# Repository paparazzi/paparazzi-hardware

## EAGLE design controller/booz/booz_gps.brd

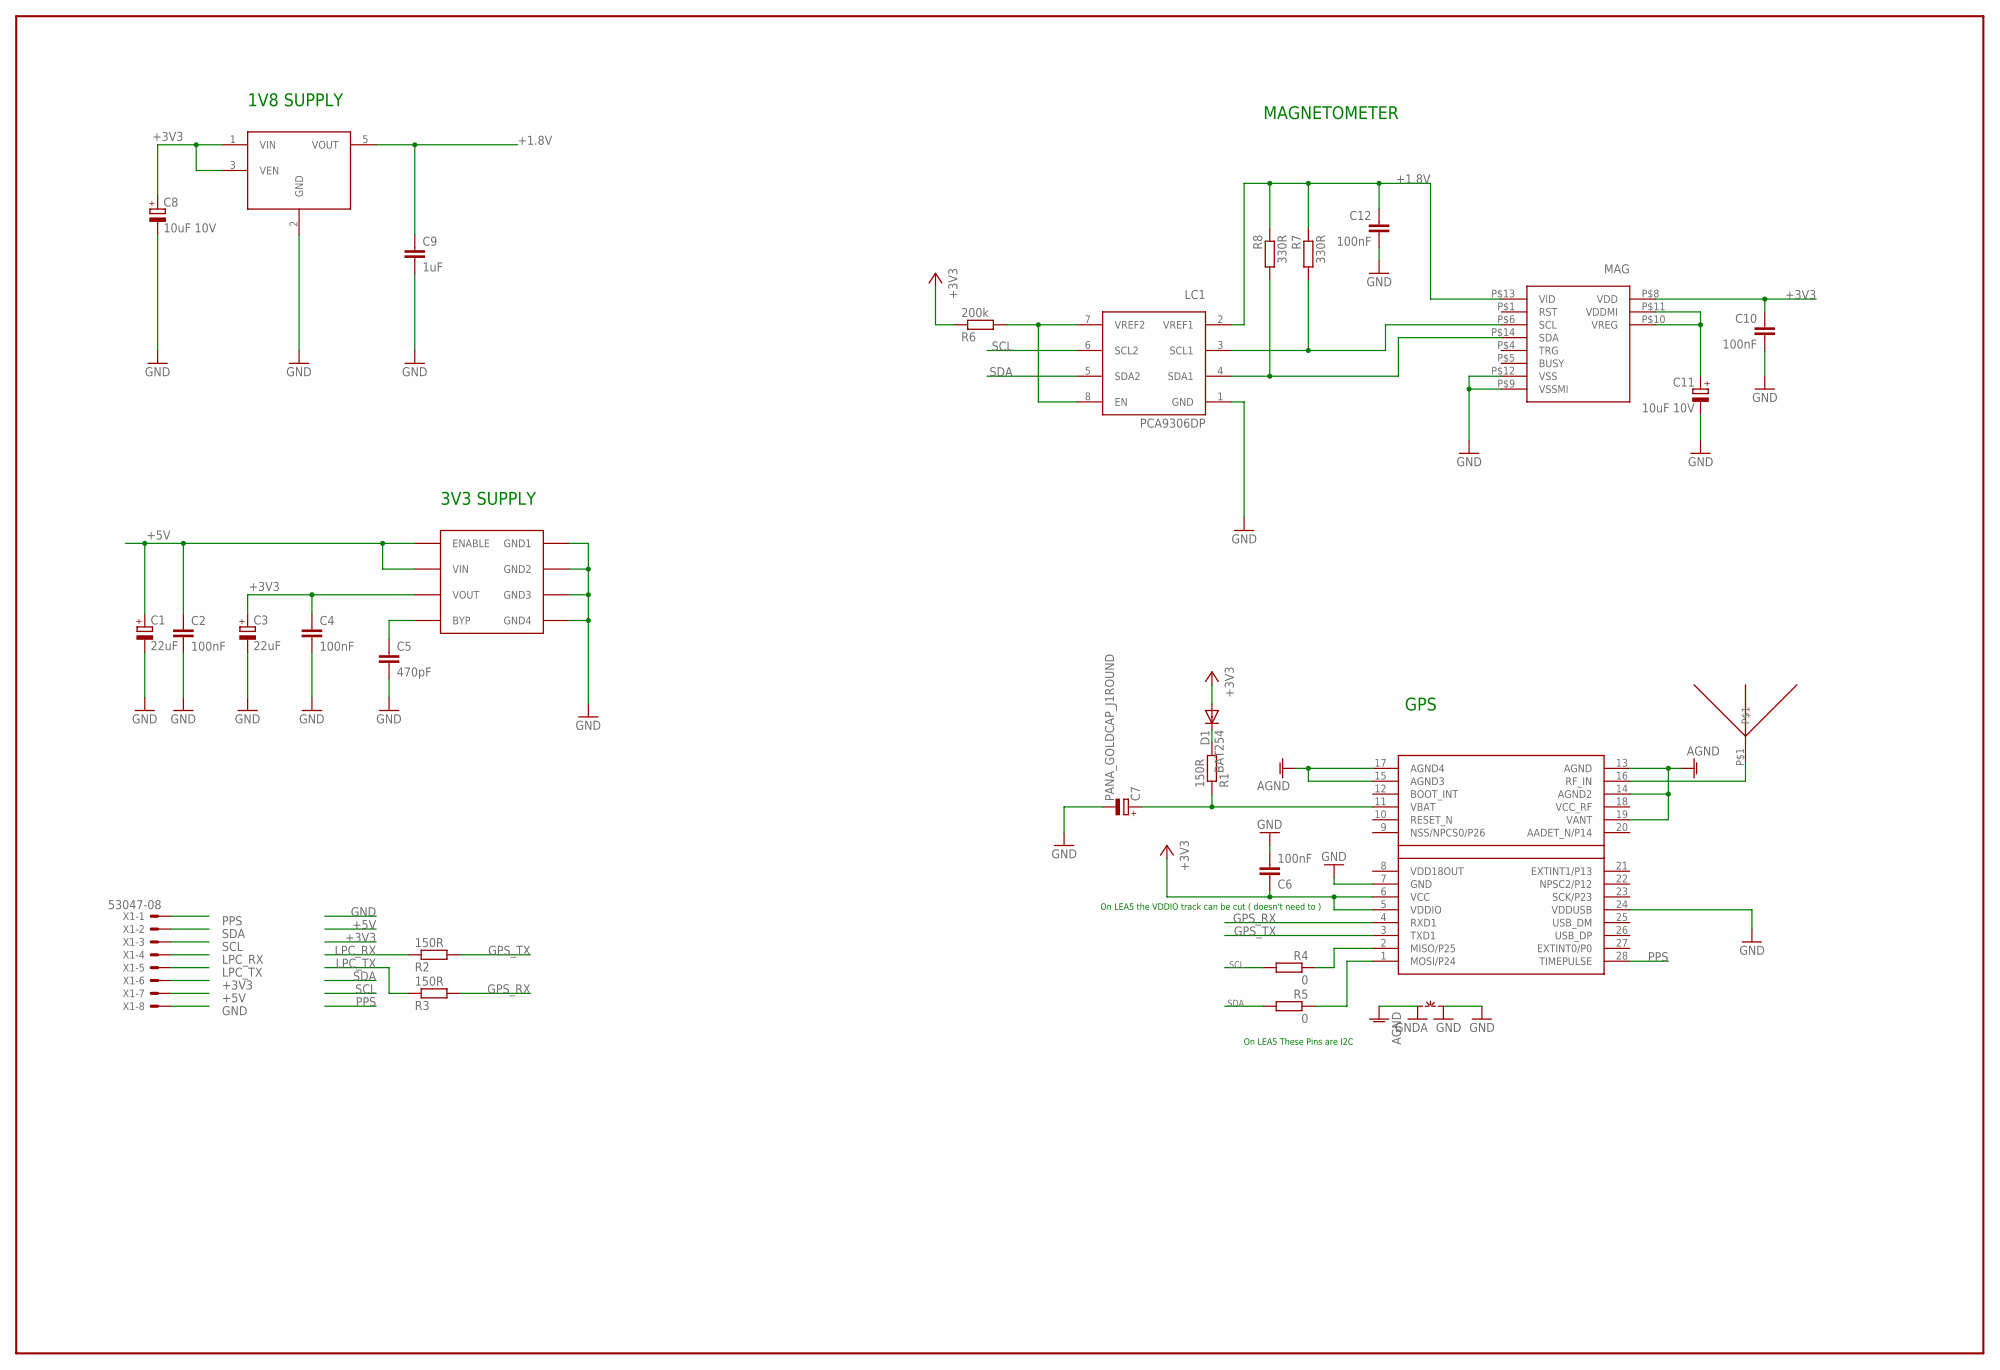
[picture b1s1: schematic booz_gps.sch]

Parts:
ANT: GPS_PATCH_ANT; SANGSHIN_1580MS18
C1, C3: 22uF; SMC_B
C2, C12: 100nF; C0603
C4, C6, C10: 100nF; C0603K
C5: 470pF; C0603K
C7: PANA_GOLDCAP_J1ROUND; PANA_J1_BIS
C8, C11: 10uF 10V; CT3216
C9: 1uF; C0805
D1: BAT254; SOD110-R
GPS: LEA-4P; LEA-LA
LC1: PCA9306DP; TSSOP_B3
MAG: AMI601
R1, R2, R3: 150R; R0603
R4, R5: 0; R0603
R6: 200k; R0603
R7, R8: 330R; R0603
VREG1: MIC5209; SOIC8
VREG2: LP3990MF; SOT23-5L
X1: 53047-08
~NUDEV~1: GND-GNDA

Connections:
+1.8V: C9.1, C12.1, LC1.2 (VREF1), MAG.P$13 (VID), R7.1, R8.1, VREG2.5 (VOUT)
+3V3: C3.+, C4.1, C6.1, C8.+, C10.1, D1.A, GPS.5 (VDDIO), GPS.6 (VCC), MAG.P$8 (VDD), R6.1, VREG1.3 (VOUT), VREG2.1 (VIN), VREG2.3 (VEN), X1.6
+5V: C1.+, C2.1, VREG1.1 (ENABLE), VREG1.2 (VIN), X1.7
AGND: GPS.13 (AGND), GPS.14 (AGND2), GPS.15 (AGND3), GPS.17 (AGND4), GPS.19 (VANT), ~NUDEV~1.GNDA
GND: C1.-, C2.2, C3.-, C4.2, C5.2, C6.2, C7.MINUS (-), C8.-, C9.2, C10.2, C11.-, C12.2, GPS.7 (GND), GPS.24 (VDDUSB), LC1.1 (GND), MAG.P$9 (VSSMI), MAG.P$12 (VSS), VREG1.5 (GND4), VREG1.6 (GND3), VREG1.7 (GND2), VREG1.8 (GND1), VREG2.2 (GND), X1.8, ~NUDEV~1.GND
GPS_RX: GPS.4 (RXD1), R3.2
GPS_TX: GPS.3 (TXD1), R2.2
LPC_RX: R2.1, X1.4
LPC_TX: R3.1, X1.5
unnamed: LC1.7 (VREF2), LC1.8 (EN), R6.2
unnamed: ANT.P$1, GPS.16 (RF_IN)
unnamed: LC1.3 (SCL1), MAG.P$6 (SCL), R7.2
unnamed: C5.1, VREG1.4 (BYP)
unnamed: C11.+, MAG.P$10 (VREG), MAG.P$11 (VDDMI)
unnamed: LC1.4 (SDA1), MAG.P$14 (SDA), R8.2
unnamed: GPS.2 (MISO/P25), R4.1
unnamed: GPS.1 (MOSI/P24), R5.1
unnamed: C7.PLUS (+), GPS.11 (VBAT), R1.1
unnamed: D1.C, R1.2
PPS: GPS.28 (TIMEPULSE), X1.1
SCL: LC1.6 (SCL2), R4.2, X1.3
SDA: LC1.5 (SDA2), R5.2, X1.2
VCC_RF: GPS.18 (VCC_RF)
VDD18OUT: GPS.8 (VDD18OUT)

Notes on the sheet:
1V8 SUPPLY
On LEA5 These Pins are I2C
3V3 SUPPLY
On LEA5 the VDDIO track can be cut ( doesn't need to )
MAGNETOMETER
GPS

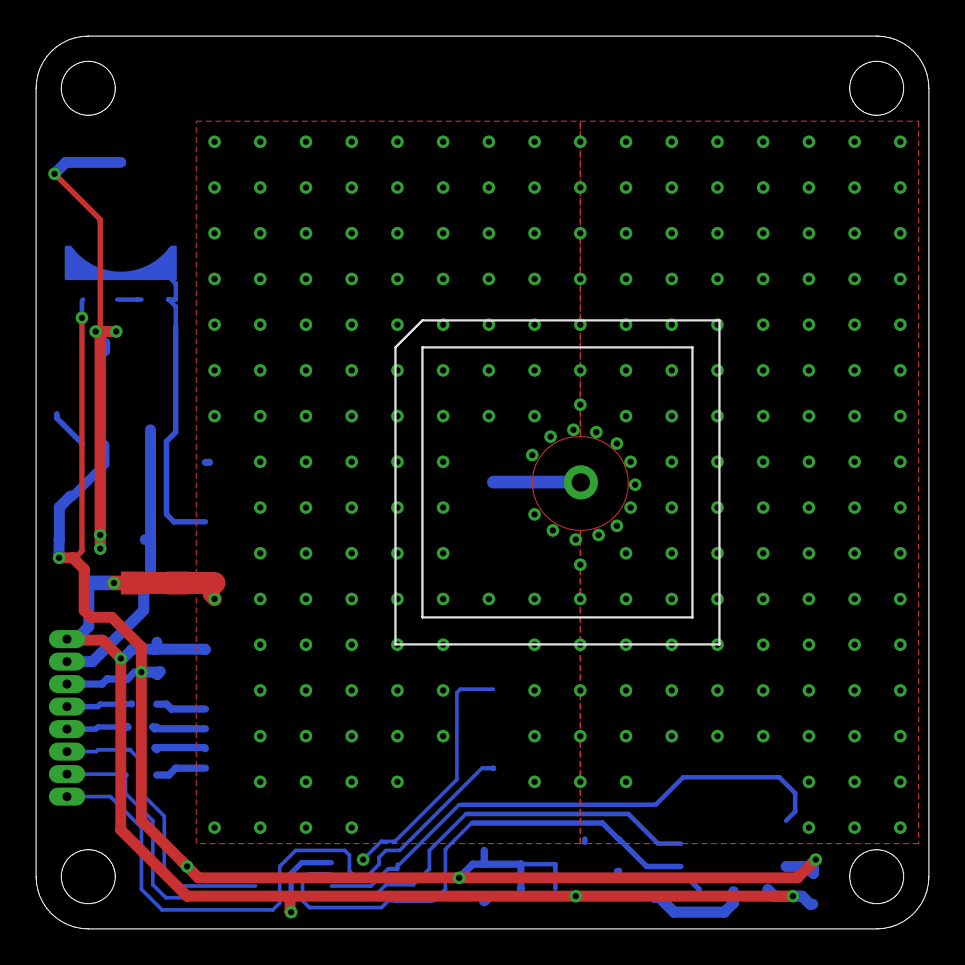
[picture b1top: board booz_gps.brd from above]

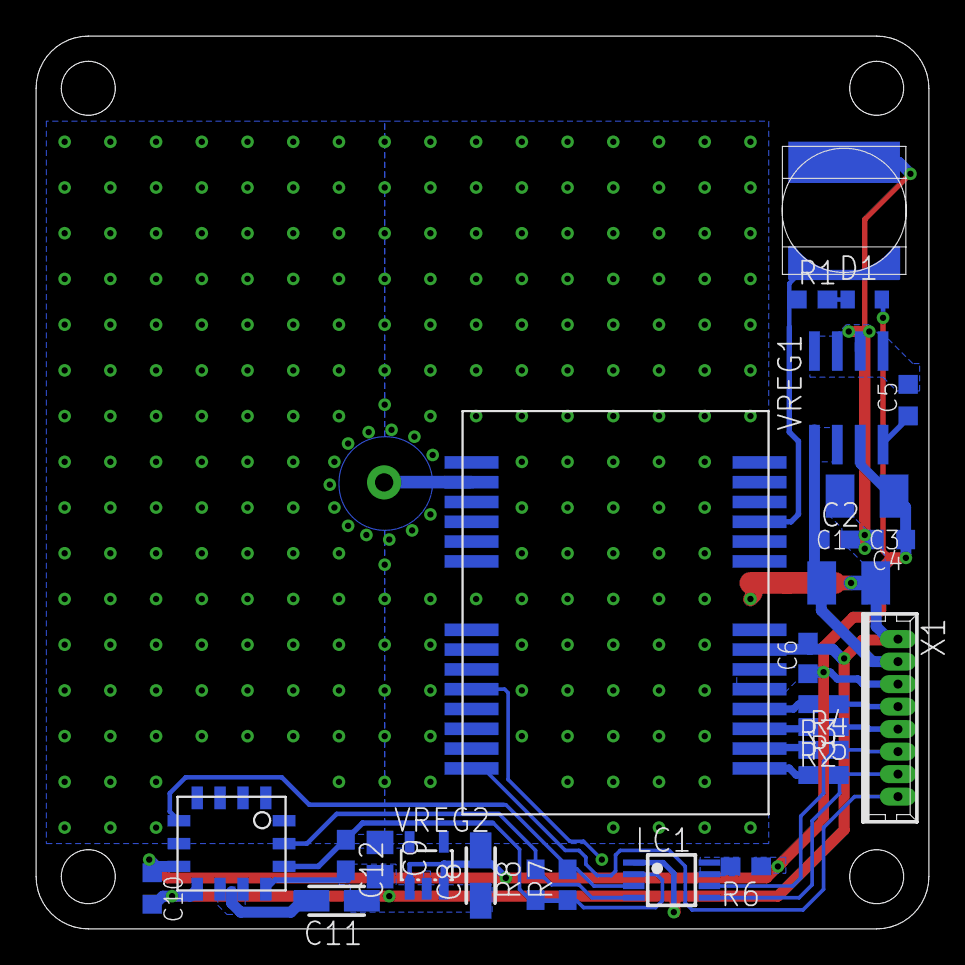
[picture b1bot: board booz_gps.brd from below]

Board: 4 copper layers, 49.6 x 49.6 mm, 29 parts (27 on the bottom side), 22 nets.

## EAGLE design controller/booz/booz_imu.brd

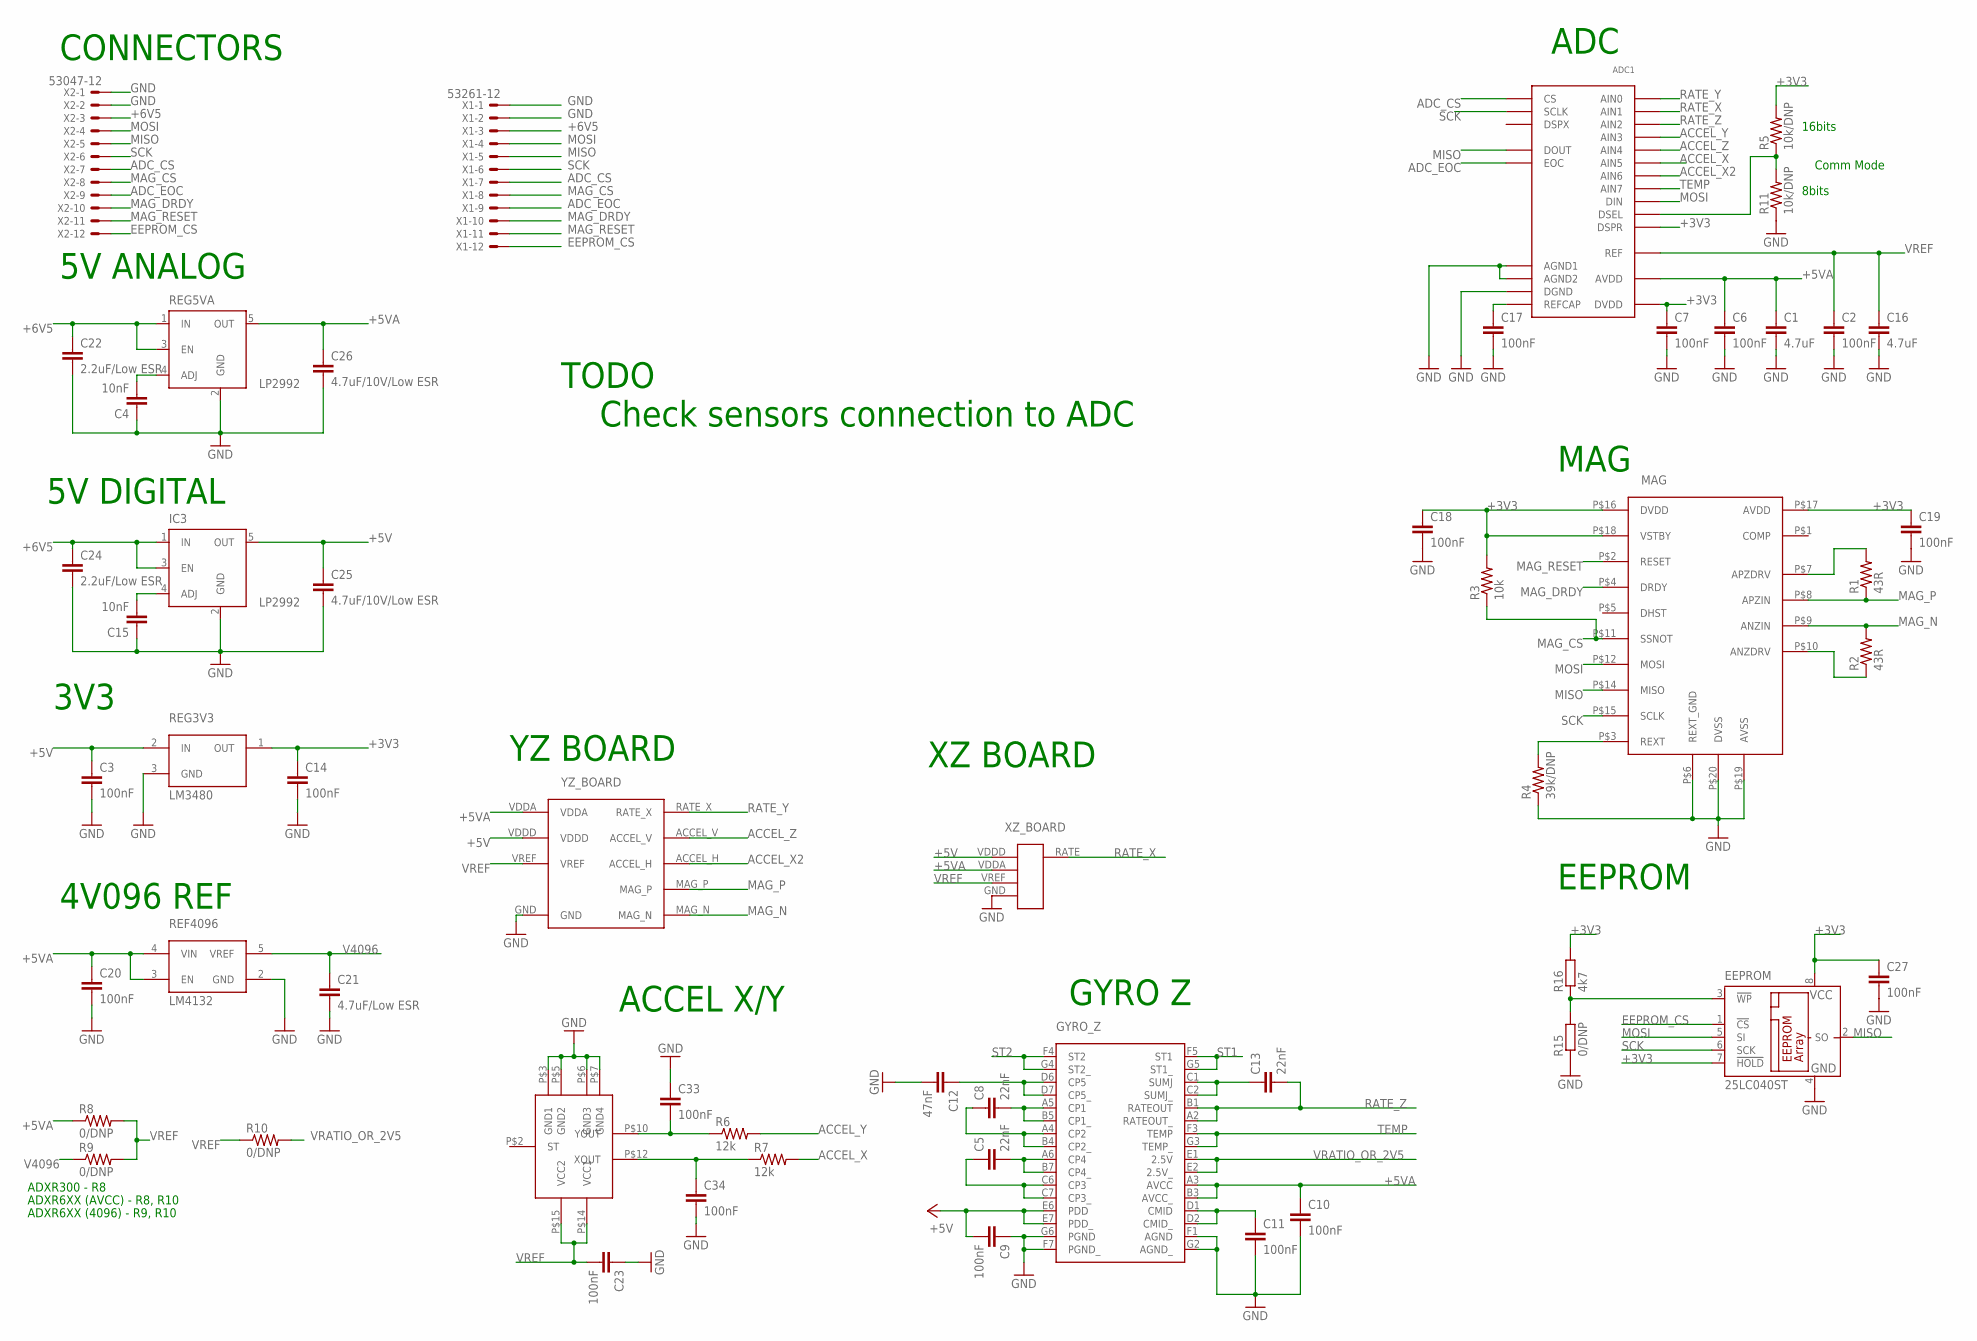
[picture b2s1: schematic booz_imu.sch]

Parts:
ADC1: MAX1168; QSOP24
C1, C16: 4.7uF; C0805
C2, C3, C6, C7, C9, C10, C11, C14, C17, C18, C19, C20, C23, C33, C34: 100nF; C0603K
C4, C15: 10nF; C0603K
C5, C8, C13: 22nF; C0603K
C12: 47nF; C0603K
C21: 4.7uF/Low ESR; C0805K
C22, C24: 2.2uF/Low ESR; C0603K
C25, C26: 4.7uF/10V/Low ESR; C0805K
C27: 100nF; C0603
EEPROM: 25LC040ST; TSSOP8
GYRO_Z: ADXR; BC-32
IC3: LP2992; SOT23-5
MAG: MS2100; QFN20
R1, R2: 43R; R0603
R3: 10k; R0603
R4: 39k/DNP; R0603
R5, R11: 10k/DNP; R0603
R6, R7: 12k; R0603
R8, R9, R10, R15: 0/DNP; R0603
R16: 4k7; R0603
REF4096: LM4132; SOT23-5L
REG3V3: LM3480; SOT23
REG5VA: LP2992; SOT23-5
U$2: ADXL320; LSCFP
X1: 53261-12
X2: 53047-12
XZ_BOARD: IMU_XZ_2; IMU_XZ
YZ_BOARD: IMU_YZ_MAG_2; IMU_YZ_MAG

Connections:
+3V3: ADC1.P$1 (DSPR), ADC1.P$22 (DVDD), C7.1, C14.1, C18.1, C19.1, C27.1, EEPROM.7 (!HOLD), EEPROM.8 (VCC), MAG.P$16 (DVDD), MAG.P$17 (AVDD), MAG.P$18 (VSTBY), R3.2, R5.2, R16.2, REG3V3.1 (OUT)
+5V: C3.1, C9.2, C25.1, GYRO_Z.E6 (PDD), GYRO_Z.E7 (PDD_), IC3.5 (OUT), REG3V3.2 (IN), XZ_BOARD.VDDD, YZ_BOARD.VDDD
+5VA: ADC1.P$19 (AVDD), C1.1, C6.1, C10.1, C20.1, C26.1, GYRO_Z.A3 (AVCC), GYRO_Z.B3 (AVCC_), R8.1, REF4096.3 (EN), REF4096.4 (VIN), REG5VA.5 (OUT), XZ_BOARD.VDDA, YZ_BOARD.VDDA
+6V5: C22.1, C24.1, IC3.1 (IN), IC3.3 (EN), REG5VA.1 (IN), REG5VA.3 (EN), X1.3, X2.3
ACCEL_X: ADC1.P$12 (AIN5), R7.2
ACCEL_X2: ADC1.P$13 (AIN6), YZ_BOARD.ACCEL_H
ACCEL_Y: ADC1.P$10 (AIN3), R6.2
ACCEL_Z: ADC1.P$11 (AIN4), YZ_BOARD.ACCEL_V
ADC_CS: ADC1.P$20 (CS), X1.7, X2.7
ADC_EOC: ADC1.P$6 (EOC), X1.9, X2.9
EEPROM_CS: EEPROM.1 (!CS), X1.12, X2.12
GND: ADC1.P$17 (AGND1), ADC1.P$18 (AGND2), ADC1.P$21 (DGND), C1.2, C2.2, C3.2, C4.1, C6.2, C7.2, C9.1, C10.2, C11.2, C12.2, C14.2, C15.1, C16.2, C17.2, C18.2, C19.2, C20.2, C21.2, C22.2, C23.1, C24.2, C25.2, C26.2, C27.2, C33.1, C34.2, EEPROM.4 (GND), GYRO_Z.F1 (AGND), GYRO_Z.F7 (PGND_), GYRO_Z.G2 (AGND_), GYRO_Z.G6 (PGND), IC3.2 (GND), MAG.P$6 (REXT_GND), MAG.P$19 (AVSS), MAG.P$20 (DVSS), R4.1, R11.1, R15.1, REF4096.2 (GND), REG3V3.3 (GND), REG5VA.2 (GND), U$2.P$3 (GND1), U$2.P$5 (GND2), U$2.P$6 (GND3), U$2.P$7 (GND4), X1.1, X1.2, X2.1, X2.2, XZ_BOARD.GND, YZ_BOARD.GND
MAG_CS: MAG.P$11 (SSNOT), R3.1, X1.8, X2.8
MAG_DRDY: MAG.P$4 (DRDY), X1.10, X2.10
MAG_N: MAG.P$9 (ANZIN), R2.2, YZ_BOARD.MAG_N
MAG_P: MAG.P$8 (APZIN), R1.1, YZ_BOARD.MAG_P
MAG_RESET: MAG.P$2 (RESET), X1.11, X2.11
MISO: ADC1.P$3 (DOUT), EEPROM.2 (SO), MAG.P$14 (MISO), X1.5, X2.5
MOSI: ADC1.P$5 (DIN), EEPROM.5 (SI), MAG.P$12 (MOSI), X1.4, X2.4
unnamed: ADC1.P$2 (DSEL), R5.1, R11.2
unnamed: ADC1.P$16 (REFCAP), C17.1
unnamed: C5.2, GYRO_Z.A6 (CP4), GYRO_Z.B7 (CP4_)
unnamed: C5.1, GYRO_Z.C6 (CP3), GYRO_Z.C7 (CP3_)
unnamed: C8.2, GYRO_Z.A5 (CP1), GYRO_Z.B5 (CP1_)
unnamed: C8.1, GYRO_Z.A4 (CP2), GYRO_Z.B4 (CP2_)
unnamed: C13.1, GYRO_Z.C1 (SUMJ), GYRO_Z.C2 (SUMJ_)
unnamed: C12.1, GYRO_Z.D6 (CP5), GYRO_Z.D7 (CP5_)
unnamed: C11.1, GYRO_Z.D1 (CMID), GYRO_Z.D2 (CMID_)
unnamed: MAG.P$10 (ANZDRV), R2.1
unnamed: MAG.P$7 (APZDRV), R1.2
unnamed: MAG.P$3 (REXT), R4.2
unnamed: C15.2, IC3.4 (ADJ)
unnamed: C33.2, R6.1, U$2.P$10 (YOUT)
unnamed: C4.2, REG5VA.4 (ADJ)
unnamed: C34.1, R7.1, U$2.P$12 (XOUT)
unnamed: EEPROM.3 (!WP), R15.2, R16.1
RATE_X: ADC1.P$8 (AIN1), XZ_BOARD.RATE
RATE_Y: ADC1.P$7 (AIN0), YZ_BOARD.RATE_X
RATE_Z: ADC1.P$9 (AIN2), C13.2, GYRO_Z.A2 (RATEOUT_), GYRO_Z.B1 (RATEOUT)
SCK: ADC1.P$4 (SCLK), EEPROM.6 (SCK), MAG.P$15 (SCLK), X1.6, X2.6
ST1: GYRO_Z.F5 (ST1), GYRO_Z.G5 (ST1_)
ST2: GYRO_Z.F4 (ST2), GYRO_Z.G4 (ST2_)
TEMP: ADC1.P$14 (AIN7), GYRO_Z.F3 (TEMP), GYRO_Z.G3 (TEMP_)
V4096: C21.1, R9.1, REF4096.5 (VREF)
VRATIO_OR_2V5: GYRO_Z.E1 (2.5V), GYRO_Z.E2 (2.5V_), R10.2
VREF: ADC1.P$15 (REF), C2.1, C16.1, C23.2, R8.2, R9.2, R10.1, U$2.P$14 (VCC1), U$2.P$15 (VCC2), XZ_BOARD.VREF, YZ_BOARD.VREF

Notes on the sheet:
5V ANALOG
5V DIGITAL
Comm Mode
ADXR300 - R8
ADXR6XX (AVCC) - R8, R10
ADXR6XX (4096) - R9, R10
3V3
4V096 REF
CONNECTORS
ADC
GYRO Z
ACCEL X/Y
XZ BOARD
YZ BOARD
MAG
EEPROM
TODO
Check sensors connection to ADC
16bits
8bits

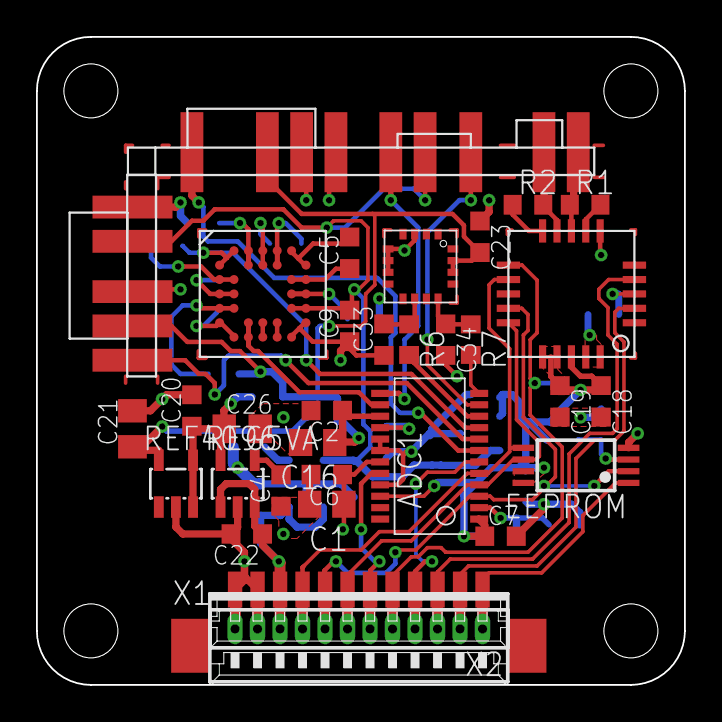
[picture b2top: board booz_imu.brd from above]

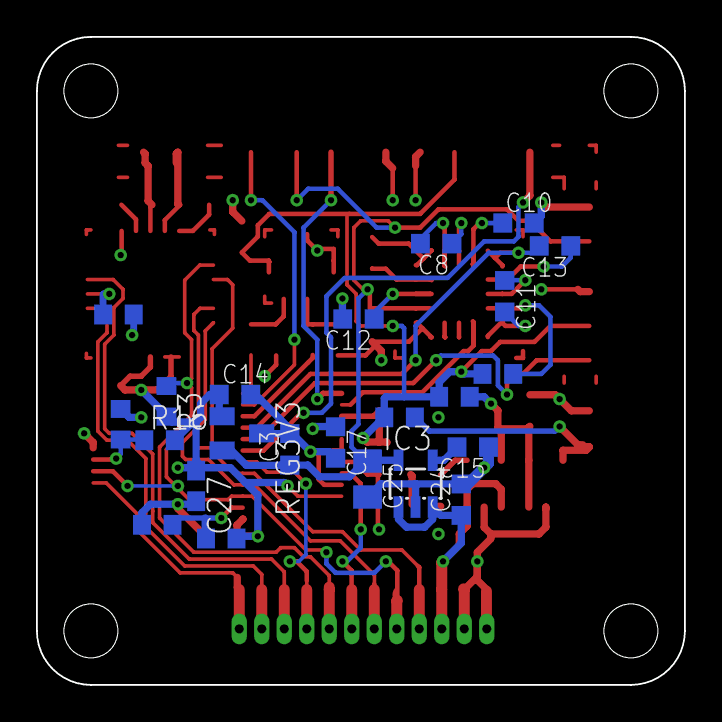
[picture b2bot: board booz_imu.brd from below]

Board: 4 copper layers, 36.0 x 36.0 mm, 55 parts (23 on the bottom side), 46 nets.

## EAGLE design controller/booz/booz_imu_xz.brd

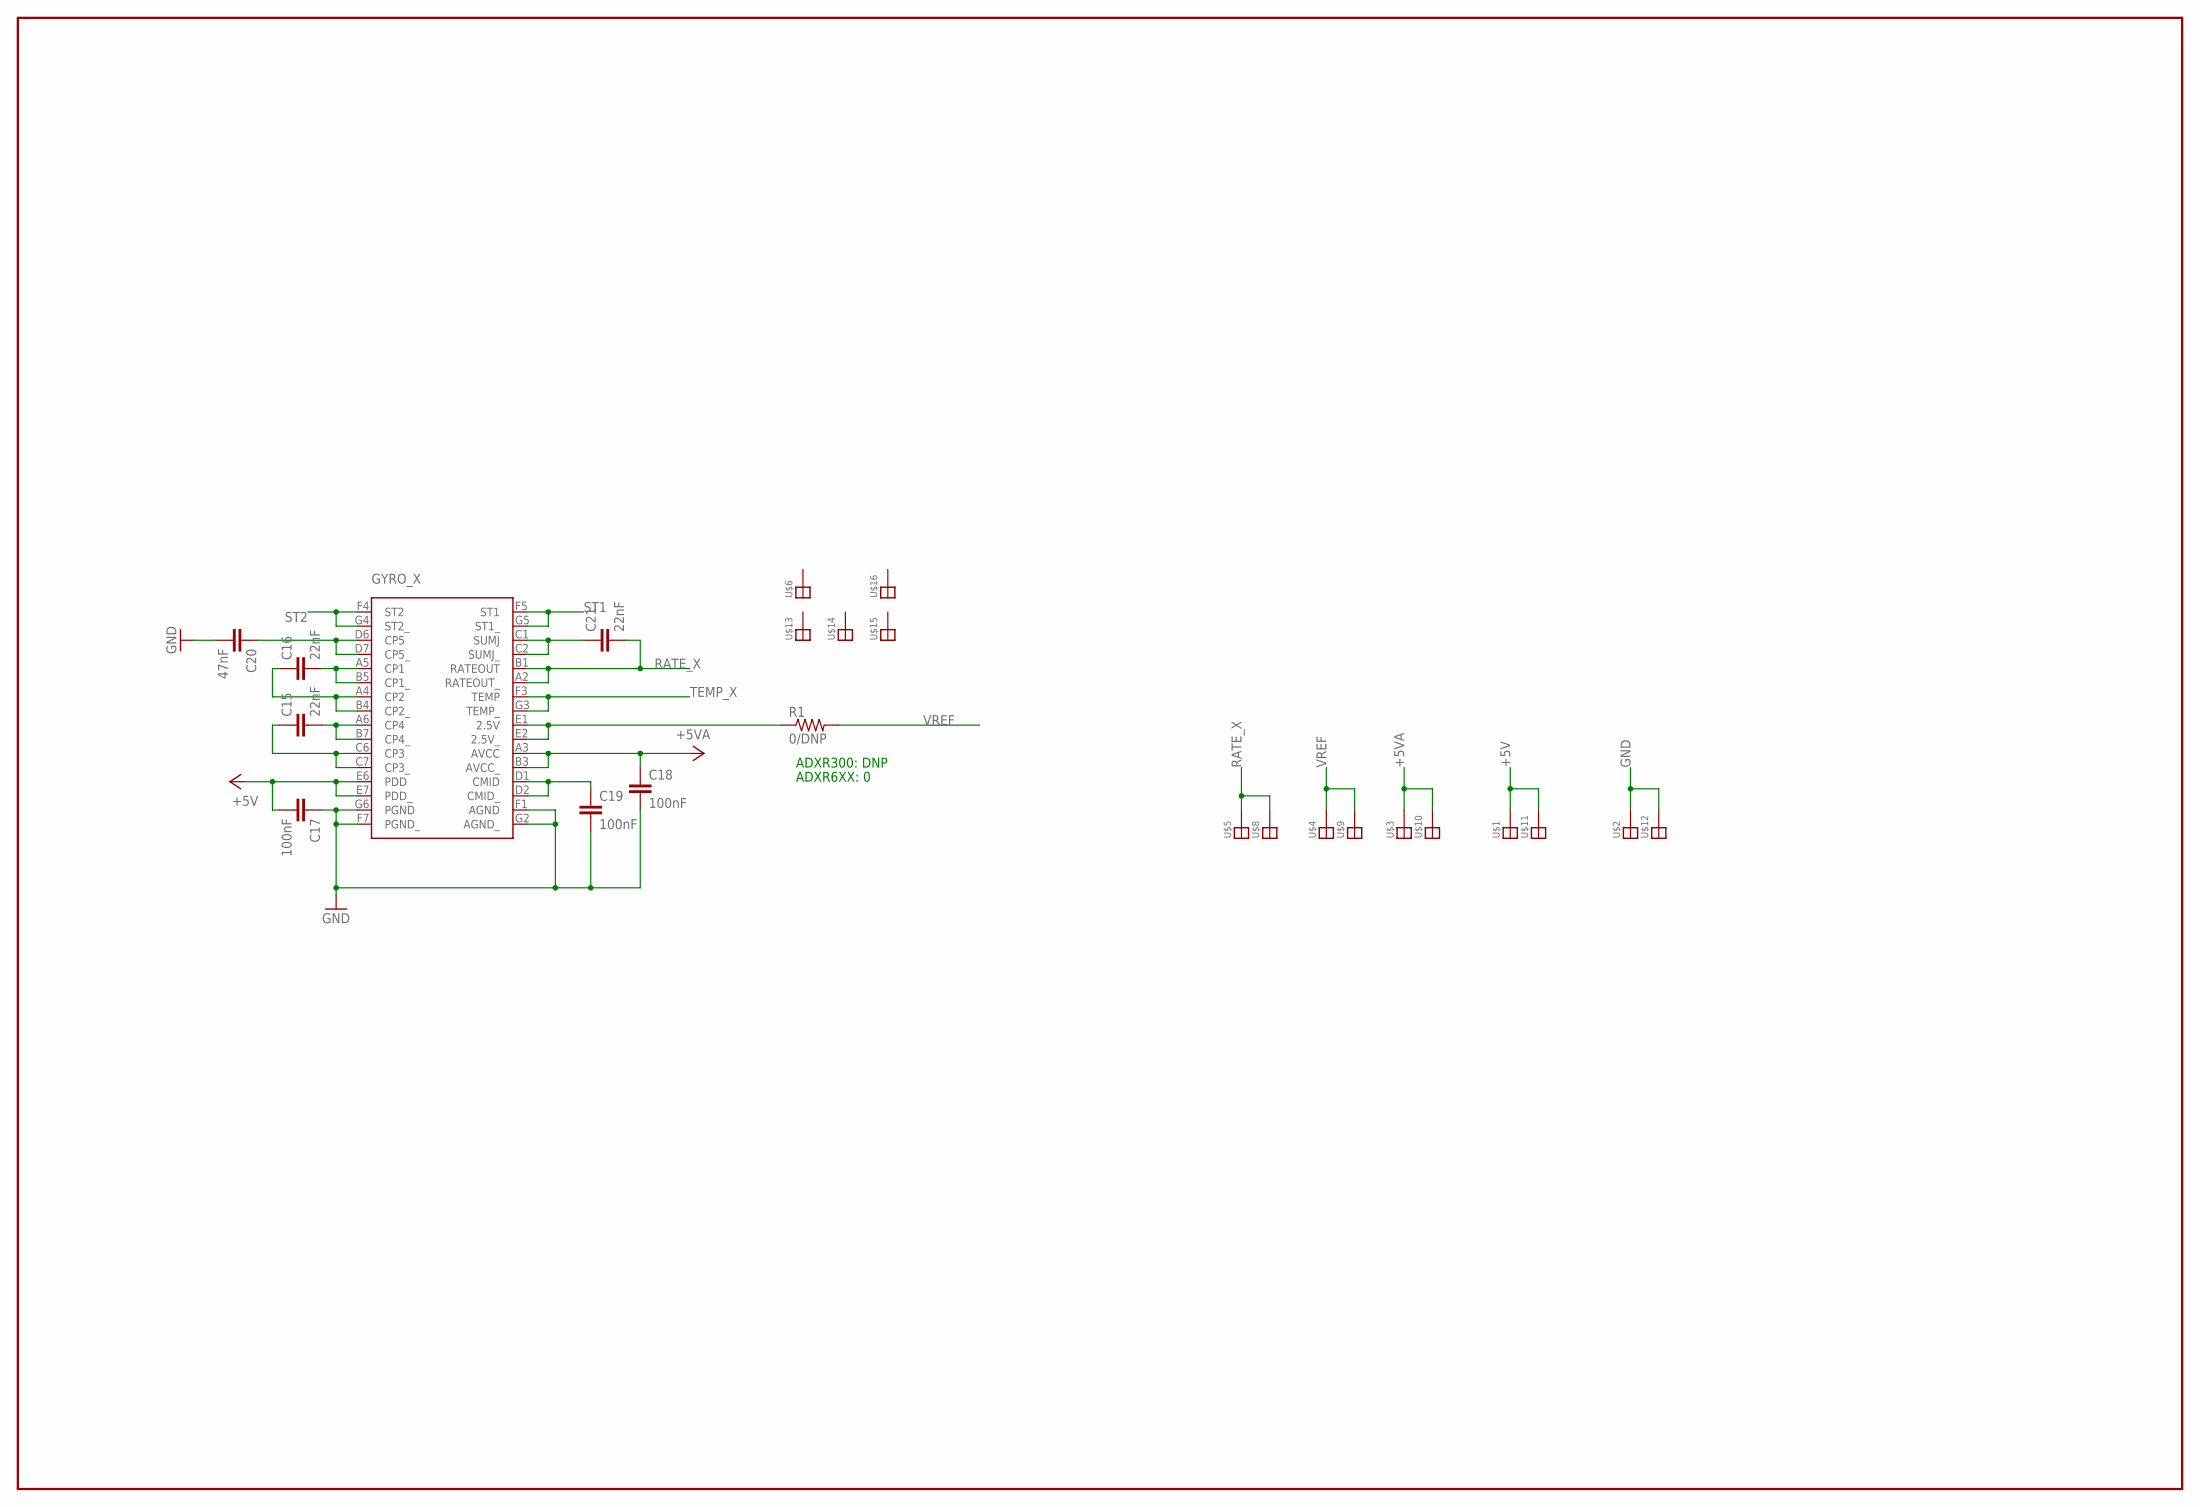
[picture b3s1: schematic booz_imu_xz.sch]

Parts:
C15, C16, C21: 22nF; C0603K
C17, C18, C19: 100nF; C0603K
C20: 47nF; C0603K
GYRO_X: ADXR; BC-32
R1: 0/DNP; R0603
U$1, U$2, U$3, U$4, U$5, U$6, U$8, U$9, U$10, U$11, U$12, U$13, U$14, U$15, U$16: SOLDER_PAD

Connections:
+5V: C17.2, GYRO_X.E6 (PDD), GYRO_X.E7 (PDD_), U$1.P$1, U$11.P$1
+5VA: C18.1, GYRO_X.A3 (AVCC), GYRO_X.B3 (AVCC_), U$3.P$1, U$10.P$1
GND: C17.1, C18.2, C19.2, C20.2, GYRO_X.F1 (AGND), GYRO_X.F7 (PGND_), GYRO_X.G2 (AGND_), GYRO_X.G6 (PGND), U$2.P$1, U$12.P$1
unnamed: C21.1, GYRO_X.C1 (SUMJ), GYRO_X.C2 (SUMJ_)
unnamed: C15.1, GYRO_X.C6 (CP3), GYRO_X.C7 (CP3_)
unnamed: C20.1, GYRO_X.D6 (CP5), GYRO_X.D7 (CP5_)
unnamed: C16.2, GYRO_X.A5 (CP1), GYRO_X.B5 (CP1_)
unnamed: C16.1, GYRO_X.A4 (CP2), GYRO_X.B4 (CP2_)
unnamed: C15.2, GYRO_X.A6 (CP4), GYRO_X.B7 (CP4_)
unnamed: GYRO_X.E1 (2.5V), GYRO_X.E2 (2.5V_), R1.1
unnamed: C19.1, GYRO_X.D1 (CMID), GYRO_X.D2 (CMID_)
RATE_X: C21.2, GYRO_X.A2 (RATEOUT_), GYRO_X.B1 (RATEOUT), U$5.P$1, U$8.P$1
ST1: GYRO_X.F5 (ST1), GYRO_X.G5 (ST1_)
ST2: GYRO_X.F4 (ST2), GYRO_X.G4 (ST2_)
TEMP_X: GYRO_X.F3 (TEMP), GYRO_X.G3 (TEMP_)
VREF: R1.2, U$4.P$1, U$9.P$1

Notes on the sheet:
ADXR300: DNP
ADXR6XX: 0

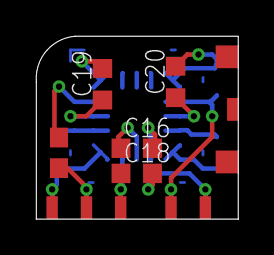
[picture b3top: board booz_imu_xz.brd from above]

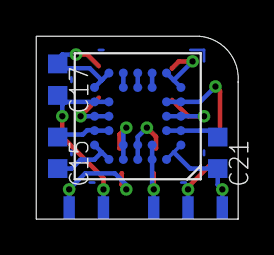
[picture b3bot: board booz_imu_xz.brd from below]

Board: 4 copper layers, 11.2 x 10.2 mm, 24 parts (9 on the bottom side), 16 nets.

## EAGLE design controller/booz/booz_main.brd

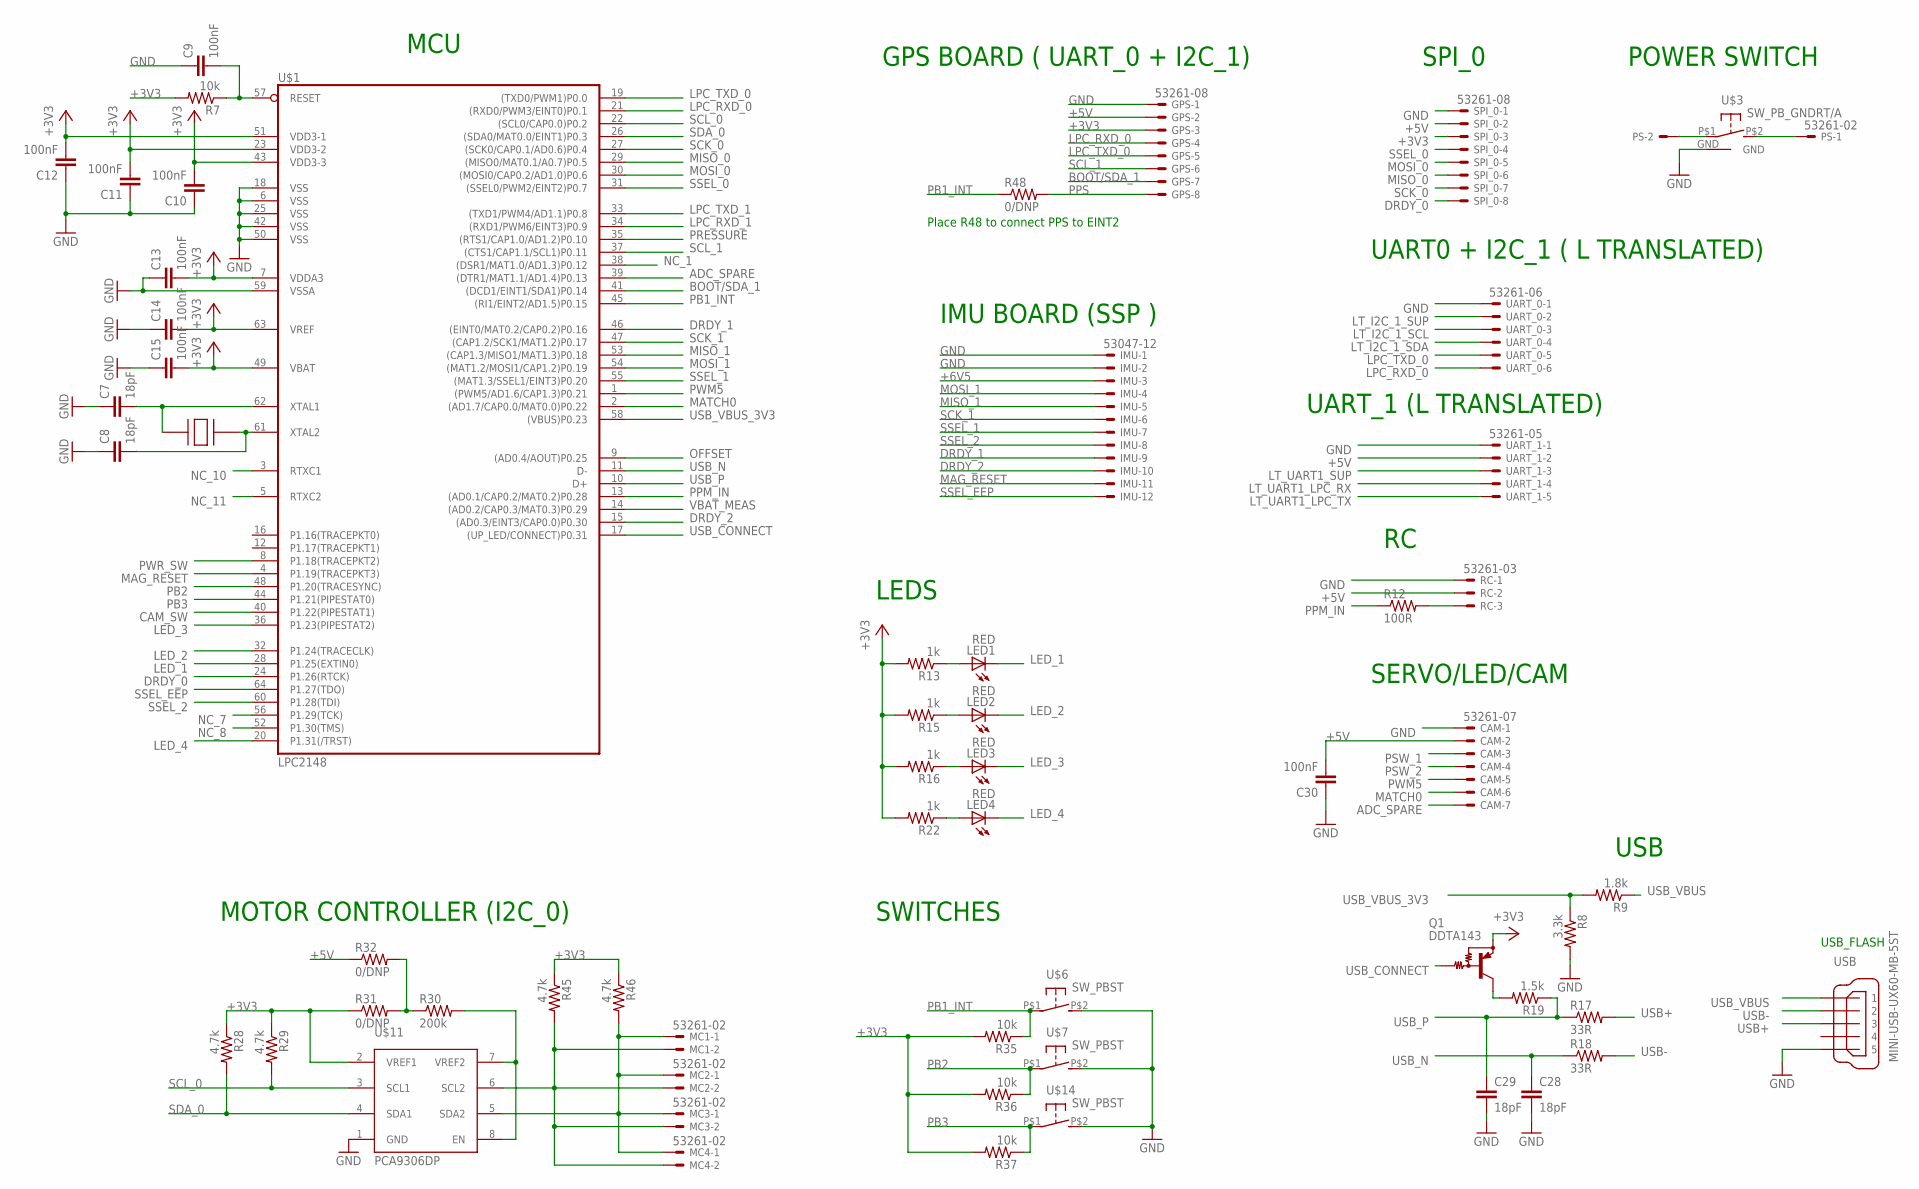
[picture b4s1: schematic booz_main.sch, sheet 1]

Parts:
C7, C8, C28, C29: 18pF; C0603
C9, C10, C11, C12, C13, C14, C15, C30: 100nF; C0603
CAM: 53261-07
GPS: 53261-08
IMU: 53047-12
LED1, LED2, LED3, LED4: RED; CHIP-LED0805
MC1, MC2, MC3, MC4: 53261-02
PS: 53261-02
Q1: DDTA143; SC59-BEC
R7, R35, R36, R37: 10k; R0603
R8: 3.3k; R0603
R9: 1.8k; R0603
R12: 100R; R0603
R13, R15, R16, R22: 1k; R0603
R17, R18: 33R; R0603
R19: 1.5k; R0603
R28, R29, R45, R46: 4.7k; R0603
R30: 200k; R0603
R31, R32, R48: 0/DNP; R0603
RC: 53261-03
SPI_0: 53261-08
U$1: LPC2148; SQFP-S-10X10-64
U$3: SW_PB_GNDRT/A; B3U-3100P
U$4: CRYSTAL_CTS; CTS_CRYSTAL
U$6, U$7, U$14: SW_PBST; B3U-1000P
U$11: PCA9306DP; TSSOP_B3
UART_0: 53261-06
UART_1: 53261-05
USB: MINI-USB-UX60-MB-5ST; UX60-MB-5ST

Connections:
+3V3: C10.2, C11.2, C12.2, C13.2, C14.2, C15.2, GPS.3, Q1.E, R7.2, R13.2, R15.2, R16.2, R22.2, R28.1, R29.1, R31.1, R35.2, R36.2, R37.2, R45.1, R46.1, SPI_0.3, U$1.7 (VDDA3), U$1.23 (VDD3-2), U$1.43 (VDD3-3), U$1.49 (VBAT), U$1.51 (VDD3-1), U$1.63 (VREF), U$11.2 (VREF1); also elsewhere on the board
+5V: C30.2, CAM.2, GPS.2, R32.1, RC.2, SPI_0.2, UART_1.2; also elsewhere on the board
+6V5: IMU.3; also elsewhere on the board
ADC_SPARE: CAM.7, U$1.39 ((DTR1/MAT1.1/AD1.4)P0.13)
BOOT/SDA_1: GPS.7, U$1.41 ((DCD1/EINT1/SDA1)P0.14); also elsewhere on the board
CAM_SW: U$1.40 (P1.22(PIPESTAT1)); also elsewhere on the board
DRDY_0: SPI_0.8, U$1.24 (P1.26(RTCK))
DRDY_1: IMU.9, U$1.46 ((EINT0/MAT0.2/CAP0.2)P0.16)
DRDY_2: IMU.10, U$1.15 ((AD0.3/EINT3/CAP0.0)P0.30)
GND: C7.1, C8.1, C9.1, C10.1, C11.1, C12.1, C13.1, C14.1, C15.1, C28.2, C29.2, C30.1, CAM.1, GPS.1, IMU.1, IMU.2, R8.2, RC.1, SPI_0.1, U$1.6 (VSS), U$1.18 (VSS), U$1.25 (VSS), U$1.42 (VSS), U$1.50 (VSS), U$1.59 (VSSA), U$3.GND, U$6.P$2 (S), U$7.P$2 (S), U$11.1 (GND), U$14.P$2 (S), UART_0.1, UART_1.1, USB.5; also elsewhere on the board
LED_1: LED1.C, U$1.28 (P1.25(EXTIN0))
LED_2: LED2.C, U$1.32 (P1.24(TRACECLK))
LED_3: LED3.C, U$1.36 (P1.23(PIPESTAT2))
LED_4: LED4.C, U$1.20 (P1.31(/TRST))
LPC_RESET: C9.2, R7.1, U$1.57 (RESET)
LPC_RXD_0: GPS.4, U$1.21 ((RXD0/PWM3/EINT0)P0.1), UART_0.6
LPC_RXD_1: U$1.34 ((RXD1/PWM6/EINT3)P0.9); also elsewhere on the board
LPC_TXD_0: GPS.5, U$1.19 ((TXD0/PWM1)P0.0), UART_0.5
LPC_TXD_1: U$1.33 ((TXD1/PWM4/AD1.1)P0.8); also elsewhere on the board
LT_I2C_1_SCL: UART_0.3; also elsewhere on the board
LT_I2C_1_SDA: UART_0.4; also elsewhere on the board
LT_I2C_1_SUP: UART_0.2; also elsewhere on the board
LT_UART1_LPC_RX: UART_1.4; also elsewhere on the board
LT_UART1_LPC_TX: UART_1.5; also elsewhere on the board
LT_UART1_SUP: UART_1.3; also elsewhere on the board
MAG_RESET: IMU.11, U$1.4 (P1.19(TRACEPKT3))
MATCH0: CAM.6, U$1.2 ((AD1.7/CAP0.0/MAT0.0)P0.22)
MISO_0: SPI_0.6, U$1.29 ((MISO0/MAT0.1/A0.7)P0.5)
MISO_1: IMU.5, U$1.53 ((CAP1.3/MISO1/MAT1.3)P0.18)
MOSI_0: SPI_0.5, U$1.30 ((MOSI0/CAP0.2/AD1.0)P0.6)
MOSI_1: IMU.4, U$1.54 ((MAT1.2/MOSI1/CAP1.2)P0.19)
unnamed: LED1.A, R13.1
unnamed: C7.2, U$1.62 (XTAL1), U$4.P$1
unnamed: R30.1, R31.2, R32.2
unnamed: C8.2, U$1.61 (XTAL2), U$4.P$3
unnamed: LED2.A, R15.1
unnamed: LED3.A, R16.1
unnamed: R30.2, U$11.7 (VREF2), U$11.8 (EN)
unnamed: PS.2, U$3.P$1
unnamed: PS.1, U$3.P$2 (S)
unnamed: Q1.C, R19.2
unnamed: R12.2, RC.3
unnamed: LED4.A, R22.1
NC_1: U$1.38 ((DSR1/MAT1.0/AD1.3)P0.12)
NC_7: U$1.56 (P1.29(TCK))
NC_8: U$1.52 (P1.30(TMS))
NC_10: U$1.3 (RTXC1)
NC_11: U$1.5 (RTXC2)
OFFSET: U$1.9 ((AD0.4/AOUT)P0.25); also elsewhere on the board
PB1_INT: R35.1, R48.1, U$1.45 ((RI1/EINT2/AD1.5)P0.15), U$6.P$1
PB2: R36.1, U$1.48 (P1.20(TRACESYNC)), U$7.P$1
PB3: R37.1, U$1.44 (P1.21(PIPESTAT0)), U$14.P$1
PPM_IN: R12.1, U$1.13 ((AD0.1/CAP0.2/MAT0.2)P0.28)
PPS: GPS.8, R48.2
PRESSURE: U$1.35 ((RTS1/CAP1.0/AD1.2)P0.10); also elsewhere on the board
PSW_1: CAM.3; also elsewhere on the board
PSW_2: CAM.4; also elsewhere on the board
PWM5: CAM.5, U$1.1 ((PWM5/AD1.6/CAP1.3)P0.21)
PWR_SW: U$1.8 (P1.18(TRACEPKT2)); also elsewhere on the board
SCK_0: SPI_0.7, U$1.27 ((SCK0/CAP0.1/AD0.6)P0.4)
SCK_1: IMU.6, U$1.47 ((CAP1.2/SCK1/MAT1.2)P0.17)
SCL_0: R29.2, U$1.22 ((SCL0/CAP0.0)P0.2), U$11.3 (SCL1)
SCL_0_TRANSLATED: MC1.2, MC2.2, MC3.2, MC4.2, R45.2, U$11.6 (SCL2)
SCL_1: GPS.6, U$1.37 ((CTS1/CAP1.1/SCL1)P0.11); also elsewhere on the board
SDA_0: R28.2, U$1.26 ((SDA0/MAT0.0/EINT1)P0.3), U$11.4 (SDA1)
SDA_0_TRANSLATED: MC1.1, MC2.1, MC3.1, MC4.1, R46.2, U$11.5 (SDA2)
SSEL_0: SPI_0.4, U$1.31 ((SSEL0/PWM2/EINT2)P0.7)
SSEL_1: IMU.7, U$1.55 ((MAT1.3/SSEL1/EINT3)P0.20)
SSEL_2: IMU.8, U$1.60 (P1.28(TDI))
SSEL_EEP: IMU.12, U$1.64 (P1.27(TDO))
USB+: R17.2, USB.3
USB-: R18.2, USB.2
USB_CONNECT: Q1.B, U$1.17 ((UP_LED/CONNECT)P0.31)
USB_N: C28.1, R18.1, U$1.11 (D-)
USB_P: C29.1, R17.1, R19.1, U$1.10 (D+)
USB_VBUS: R9.1, USB.1
USB_VBUS_3V3: R8.1, R9.2, U$1.58 ((VBUS)P0.23)
VBAT_MEAS: U$1.14 ((AD0.2/CAP0.3/MAT0.3)P0.29); also elsewhere on the board

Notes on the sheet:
MCU
LEDS
USB_FLASH
SPI_0
UART0 + I2C_1 ( L TRANSLATED)
MOTOR CONTROLLER (I2C_0)
USB
POWER SWITCH
SERVO/LED/CAM
GPS BOARD ( UART_0 + I2C_1)
IMU BOARD (SSP )
UART_1 (L TRANSLATED)
SWITCHES
Place R48 to connect PPS to EINT2
